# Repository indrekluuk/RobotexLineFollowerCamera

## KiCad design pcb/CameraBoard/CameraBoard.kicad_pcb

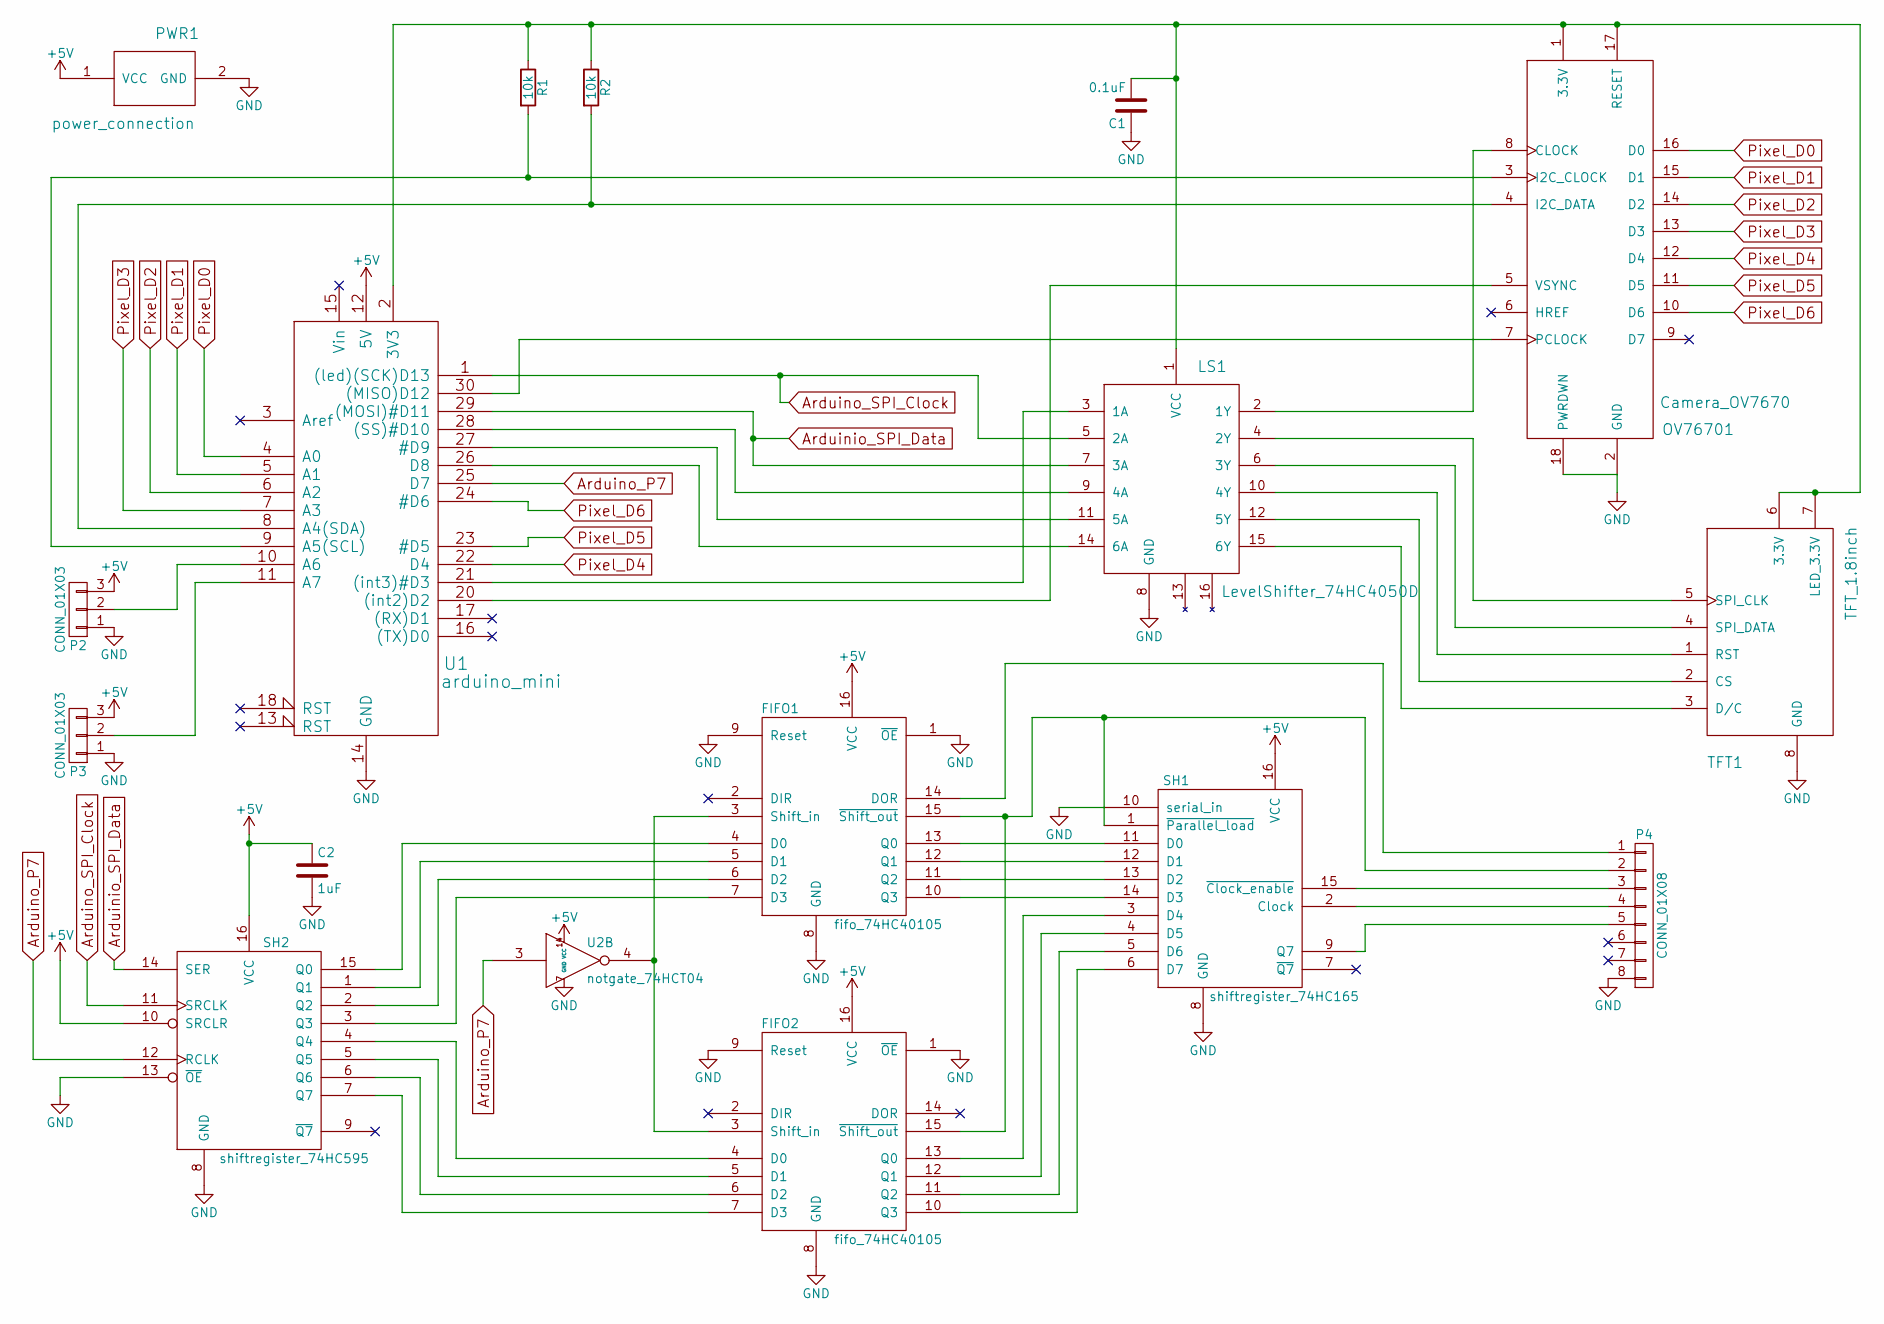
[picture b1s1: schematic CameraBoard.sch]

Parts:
C1: 0.1uF; C_1206_HandSoldering
C2: 1uF; C_1206_HandSoldering
FIFO1, FIFO2: fifo_74HC40105; SOIC-16_3.9x9.9mm_Pitch1.27mm
LS1: LevelShifter_74HC4050D; SOIC-16_3.9x9.9mm_Pitch1.27mm
OV76701: Camera_OV7670; Pin_Header_Straight_2x09
P2, P3: CONN_01X03; Pin_Header_Straight_1x03
P4: CONN_01X08; Pin_Header_Straight_2x04
PWR1: power_connection; Pin_Header_Straight_1x02
R1, R2: 10k; R_1206_HandSoldering
SH1: shiftregister_74HC165; SOIC-16_3.9x9.9mm_Pitch1.27mm
SH2: shiftregister_74HC595; SOIC-16_3.9x9.9mm_Pitch1.27mm
TFT1: TFT_1.8inch; Pin_Header_Straight_2x04
U1: arduino_mini
U2: notgate_74HCT04; SOIC-14_3.9x8.7mm_Pitch1.27mm

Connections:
+5V: C2.1, FIFO1.16 (VCC), FIFO2.16 (VCC), P2.3, P3.3, PWR1.1 (VCC), SH1.16 (VCC), SH2.10 (SRCLR), SH2.16 (VCC), U1.12 (5V), U2.14 (VCC)
Arduinio_SPI_Data: LS1.7 (3A), SH2.14 (SER), U1.29 ((MOSI)#D11)
Arduino_P7: SH2.12 (RCLK), U1.25 (D7), U2.3
Arduino_SPI_Clock: LS1.5 (2A), SH2.11 (SRCLK), U1.1 ((led)(SCK)D13)
GND: C1.1, C2.2, FIFO1.1 (~OE), FIFO1.8 (GND), FIFO1.9 (Reset), FIFO2.1 (~OE), FIFO2.8 (GND), FIFO2.9 (Reset), LS1.8 (GND), OV76701.2 (GND), OV76701.18 (PWRDWN), P2.1, P3.1, P4.8, PWR1.2 (GND), SH1.8 (GND), SH1.10 (serial_in), SH2.8 (GND), SH2.13 (~OE), TFT1.8 (GND), U1.14 (GND), U1.19 (GND), U2.7 (GND)
unnamed: C1.2, LS1.1 (VCC), OV76701.1 (3.3V), OV76701.17 (RESET), R1.1, R2.1, TFT1.6 (3.3V), TFT1.7 (LED_3.3V), U1.2 (3V3)
unnamed: FIFO1.3 (Shift_in), FIFO2.3 (Shift_in), U2.4
unnamed: FIFO1.4 (D0), SH2.15 (Q0)
unnamed: FIFO1.5 (D1), SH2.1 (Q1)
unnamed: FIFO1.6 (D2), SH2.2 (Q2)
unnamed: FIFO1.7 (D3), SH2.3 (Q3)
unnamed: FIFO1.10 (Q3), SH1.14 (D3)
unnamed: FIFO1.11 (Q2), SH1.13 (D2)
unnamed: FIFO1.12 (Q1), SH1.12 (D1)
unnamed: FIFO1.13 (Q0), SH1.11 (D0)
unnamed: FIFO1.14 (DOR), P4.1
unnamed: FIFO1.15 (~Shift_out), FIFO2.15 (~Shift_out), P4.2, SH1.1 (~Parallel_load)
unnamed: FIFO2.4 (D0), SH2.4 (Q4)
unnamed: FIFO2.5 (D1), SH2.5 (Q5)
unnamed: FIFO2.6 (D2), SH2.6 (Q6)
unnamed: FIFO2.7 (D3), SH2.7 (Q7)
unnamed: FIFO2.10 (Q3), SH1.6 (D7)
unnamed: FIFO2.11 (Q2), SH1.5 (D6)
unnamed: FIFO2.12 (Q1), SH1.4 (D5)
unnamed: FIFO2.13 (Q0), SH1.3 (D4)
unnamed: LS1.2 (1Y), OV76701.8 (CLOCK)
unnamed: LS1.3 (1A), U1.21 ((int3)#D3)
unnamed: LS1.4 (2Y), TFT1.5 (SPI_CLK)
unnamed: LS1.6 (3Y), TFT1.4 (SPI_DATA)
unnamed: LS1.9 (4A), U1.28 ((SS)#D10)
unnamed: LS1.10 (4Y), TFT1.1 (RST)
unnamed: LS1.11 (5A), U1.27 (#D9)
unnamed: LS1.12 (5Y), TFT1.2 (CS)
unnamed: LS1.14 (6A), U1.26 (D8)
unnamed: LS1.15 (6Y), TFT1.3 (D/C)
unnamed: OV76701.3 (I2C_CLOCK), R1.2, U1.9 (A5(SCL))
unnamed: OV76701.4 (I2C_DATA), R2.2, U1.8 (A4(SDA))
unnamed: OV76701.5 (VSYNC), U1.20 ((int2)D2)
unnamed: OV76701.7 (PCLOCK), U1.30 ((MISO)D12)
unnamed: P2.2, U1.10 (A6)
unnamed: P3.2, U1.11 (A7)
unnamed: P4.3, SH1.15 (~Clock_enable)
unnamed: P4.4, SH1.2 (Clock)
unnamed: P4.5, SH1.9 (Q7)
Pixel_D0: OV76701.16 (D0), U1.4 (A0)
Pixel_D1: OV76701.15 (D1), U1.5 (A1)
Pixel_D2: OV76701.14 (D2), U1.6 (A2)
Pixel_D3: OV76701.13 (D3), U1.7 (A3)
Pixel_D4: OV76701.12 (D4), U1.22 (D4)
Pixel_D5: OV76701.11 (D5), U1.23 (#D5)
Pixel_D6: OV76701.10 (D6), U1.24 (#D6)

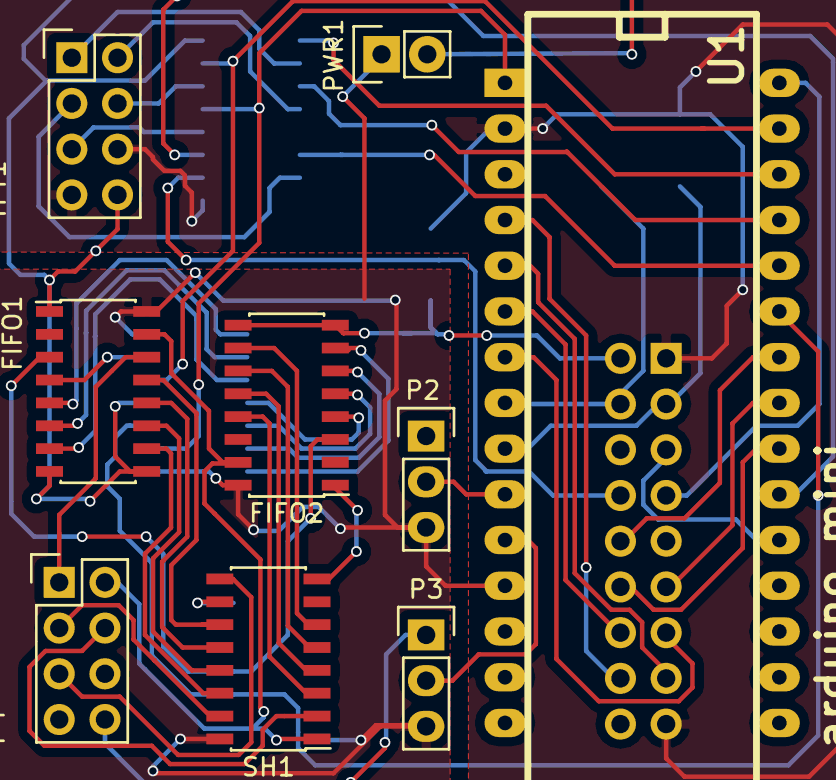
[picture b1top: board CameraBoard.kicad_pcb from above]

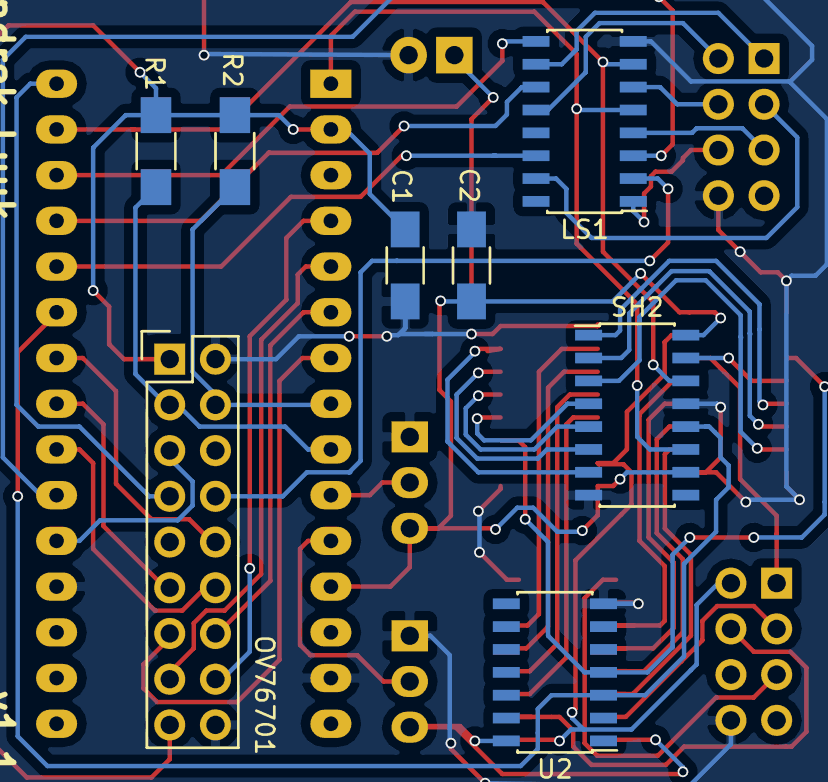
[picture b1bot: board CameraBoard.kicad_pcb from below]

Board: 2 copper layers, 17 parts (8 on the bottom side), 51 nets.

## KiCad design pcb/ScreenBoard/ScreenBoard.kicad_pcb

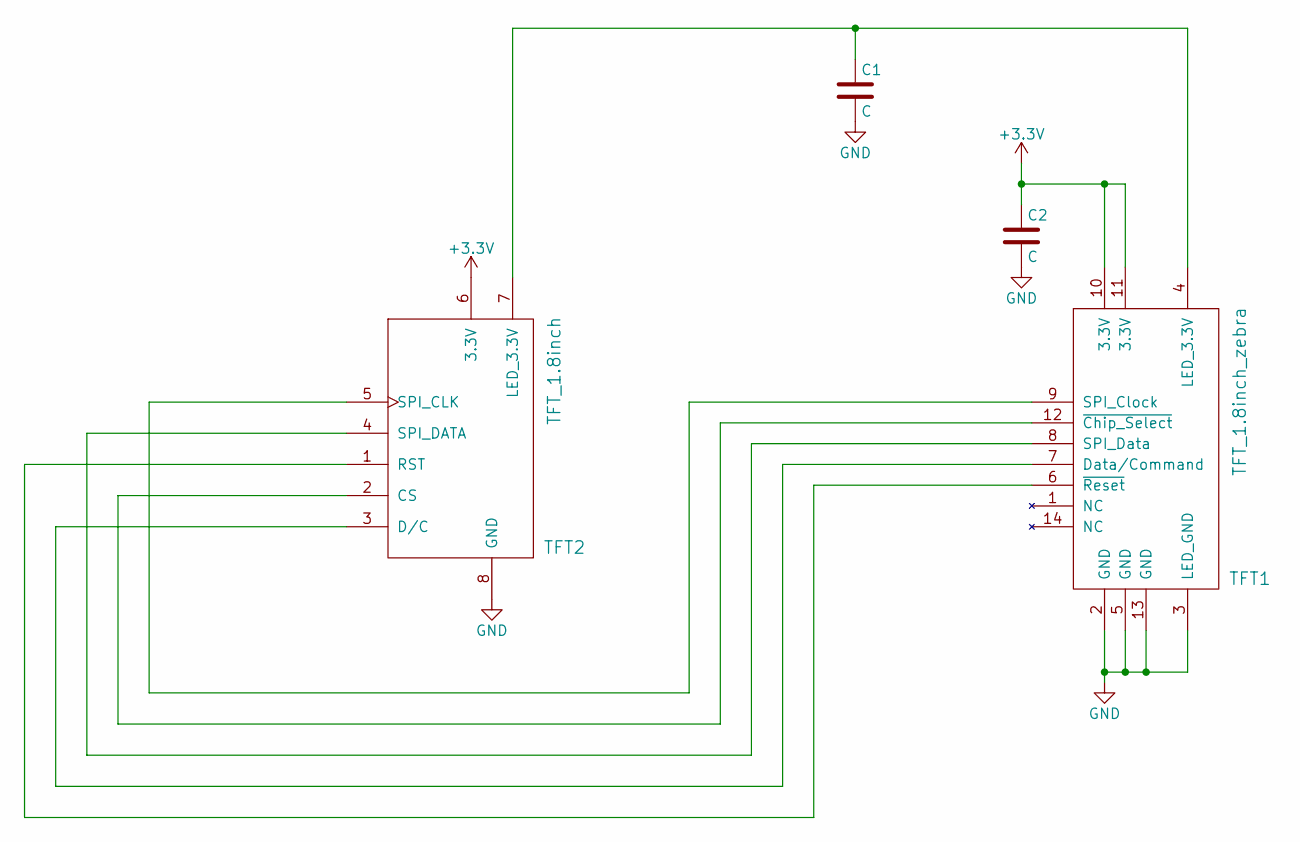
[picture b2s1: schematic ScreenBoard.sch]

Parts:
C1, C2: C; C_1206_HandSoldering
TFT1: TFT_1.8inch_zebra; ZebraStrip14_0.8mm
TFT2: TFT_1.8inch; Pin_Header_Straight_2x04

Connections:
+3V3: C2.1, TFT1.10 (3.3V), TFT1.11 (3.3V), TFT2.6 (3.3V)
GND: C1.2, C2.2, TFT1.2 (GND), TFT1.3 (LED_GND), TFT1.5 (GND), TFT1.13 (GND), TFT2.8 (GND)
unnamed: C1.1, TFT1.4 (LED_3.3V), TFT2.7 (LED_3.3V)
unnamed: TFT1.6 (~Reset), TFT2.1 (RST)
unnamed: TFT1.7 (Data/Command), TFT2.3 (D/C)
unnamed: TFT1.8 (SPI_Data), TFT2.4 (SPI_DATA)
unnamed: TFT1.9 (SPI_Clock), TFT2.5 (SPI_CLK)
unnamed: TFT1.12 (~Chip_Select), TFT2.2 (CS)

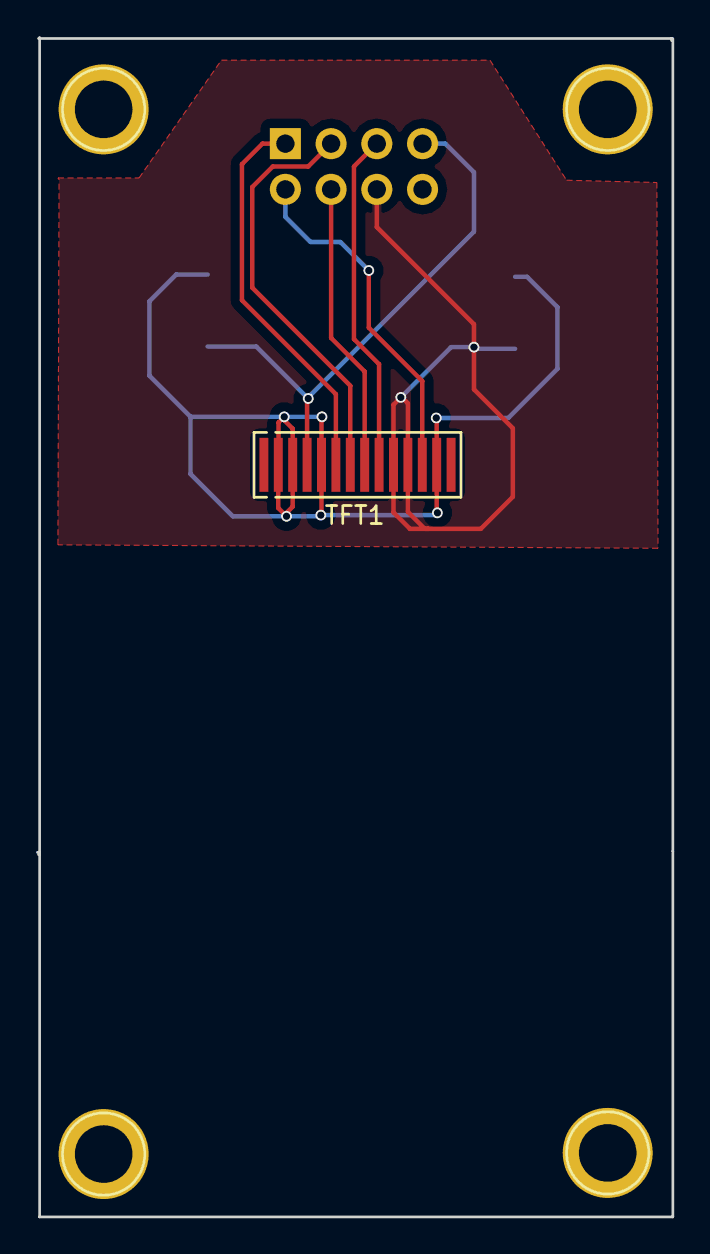
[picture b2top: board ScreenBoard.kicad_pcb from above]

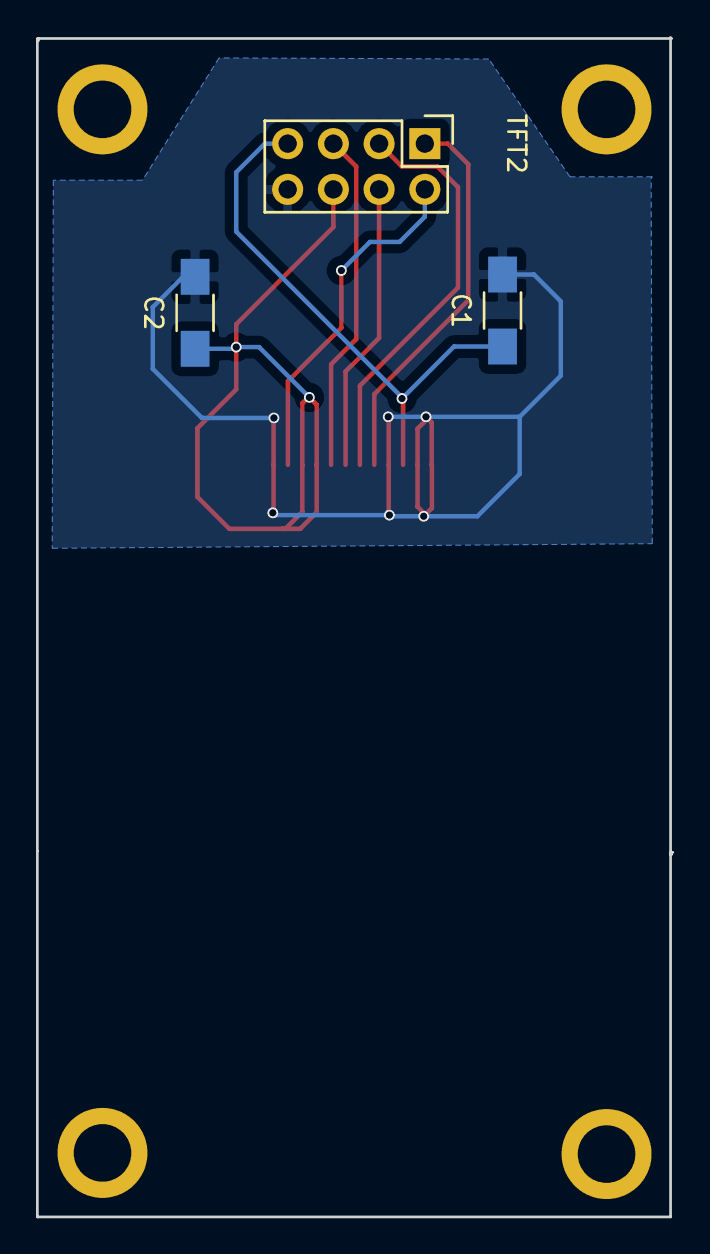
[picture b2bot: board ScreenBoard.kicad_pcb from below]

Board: 2 copper layers, 35.3 x 65.5 mm, 4 parts (3 on the bottom side), 8 nets.

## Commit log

2016-04-26 working grayscale
2016-04-26 optimized greyscale
2016-04-26 added RGB greyscale table
2016-04-30 renamed files
2016-04-30 resultion specific class
2016-04-30 camera code separated to its own file
2016-04-30 virtual function to force compile time method check
2016-04-30 configure pixel format
2016-04-30 move code to header file
2016-04-30 moved buffering to template
2016-04-30 Pixel buffer with shifted output
2016-04-30 removed unnecessary file
2016-04-30 separated grayscale table to its own file
2016-04-30 5Hz with loop
2016-04-30 unified class for below 10hz
2016-04-30 wait for 5Hz
2016-04-30 code clean-up
2016-05-07 updated camera library
2016-05-07 calculate average
2016-05-07 refactored main file
2016-05-08 improvements
2016-05-08 optimized
2016-05-08 reduce monochrome resolution to get more calculation time
2016-05-11 method for reversing bits
2016-05-13 added PCB - in progress
2016-05-15 PCB with FIFO
2016-05-15 PCB footprints are not set
2016-05-15 PCB fully wired
2016-05-16 generated gerber files
2016-06-11 Fixed NOT gate footprint
2016-07-10 moved camera board pcb to sub-folder
2016-07-10 added screen board
2016-07-10 removed labels from screw holes
2016-09-07 code is now working with new camera board
2016-09-20 send data to shift register
2016-10-02 renamed methods
2016-10-03 fixed PCB
2016-10-30 init all camera related items at one place
2016-10-30 restructured project
2016-10-30 added gtest to project
2016-10-30 added working example tests
2016-11-06 refactored code
2016-11-06 template buffer size type
2016-11-06 removed unnecessary parameters
2016-11-06 smaller buffer for grayscale
2016-11-06 camera library update
2016-11-06 ignore pdf
2016-11-06 buffer shift is not necessary from black and white image
2016-11-06 methods for writing grayscale bytes to screen
2016-11-06 alternating monochrome and grayscale lines
2016-11-06 line index
2016-11-07 new buffered camera for 80x120 grayscale
2016-11-07 separate buffer for monochrome
2016-11-08 send line location over data bus
2016-11-08 working solution
2016-11-12 14 bit monochrome buffer
2016-11-12 send pixel line over data line
2016-11-12 shifted lower byte by one
2016-11-13 removed line
2016-11-13 optimized screen cycles
2016-11-13 faster addressStart
2016-11-13 removed duplicated code
2016-11-13 reorganized code
2016-11-14 preparations for line detection
2016-11-15 re-organized CMakeLists.txt
2016-11-15 test line
2016-11-16 line detection working
2016-11-16 line as template
2016-11-16 follow connected line
2016-11-19 fixed pixel delay
2016-11-20 step detection
2016-11-20 process by segments
2016-11-20 wider line
2016-11-20 line
2016-11-20 fixed rowIndex
2016-11-20 fixed row detection if no row from the start of the screen
2016-11-20 fixed split
2016-11-20 fixed line if segments didn't touch
2016-11-20 removed duplicating test
2016-11-20 fixed start looking for line at the mid-point
2016-11-20 refactored LineStep to its own file
2016-11-20 step continuation
2016-11-20 better connection check
2016-11-20 get minimum to edge
2016-11-20 fixed typo
2016-11-20 alternating pixel color
2016-11-22 unified names
2016-11-22 ignore generated files
2016-11-23 new slope calculation
2016-11-23 fixed blue line
2016-11-23 first screen test
2016-11-24 captured screen test
2016-11-24 first screen capture test successful
2016-11-24 fixed slope calculation
2016-11-24 spreadsheet for slope calculation
2016-11-24 send line for capture
2016-11-24 fixed data mask
2016-11-25 print calculated slope value
2016-11-25 fixed bottom slope calculation
2016-11-25 adjusted slope delta
2016-11-25 but back inline attribute
2016-11-25 test case 3
2016-11-25 test case 4
2016-11-25 test case 5 (failing)
2016-11-26 new edge detection logic
2016-11-26 moved screen test to separate class
2016-11-26 all tests passing
2016-11-26 additional tests
2016-11-26 fixed line edge reset
2016-11-26 if first step is longer than the second step then use that as a reference
2016-11-26 fixed first step position value
2016-11-26 first step can not start from the edge of the screen
2016-11-26 ignore first line
2016-11-26 ignore first 5 lines
2016-11-26 send identified line
2016-11-26 frame capture printout directly in camera Arduino
2016-11-27 removed unnecessary comments
2016-11-27 do not start line if it is detected from bottom corners (camera can see the wheel)
2016-11-28 lower threshold for line detection
2016-11-28 16 line stripes
2016-11-28 if line is already found then do disable corner disabling
2016-11-28 move detected line to edge if line segment touches edge
2016-11-29 minimum line detection start range
2016-11-29 fixed tests
2016-11-29 use bitfield structure for message
2016-11-29 store before and after segments
2016-11-29 removed red lines
2016-11-29 detect sharp turn
2016-11-29 fixed sharp turn direction
2016-11-29 detect segment jump
2016-11-30 removed sharp turn detection. Too flaky
2016-11-30 detect crossing
2016-11-30 remove turn detection delay
2016-11-30 failing test for line split
2016-11-30 renamed class
2016-11-30 refactored inner structure
2016-11-30 split sections
2016-11-30 detect split
2016-12-01 process line split
2016-12-01 fixed end of line
2016-12-01 improved split line printout
2016-12-01 stop Line after line found
2016-12-01 split detection fix
2016-12-01 80 pixel grayscale does not need unrolled pixel reading
2016-12-01 fixed split detection
2016-12-01 renamed methods to be more descriptive
2016-12-01 fixed all tests
2016-12-01 fixed grayscale image
2016-12-01 restore ignore zone
2016-12-02 moved line turn ignore check to more correct location
2016-12-02 cancel line search if line jump
2016-12-02 fixed line detection if line takes whole screen
2016-12-02 for second line choose closest to middle
2016-12-02 make row top more visible
2016-12-02 use segment center after split detection
2016-12-02 for sub-sequent splits choose closest to the middle
2016-12-02 do not force line to edge
2016-12-02 show identified line
2016-12-02 turn on capture mode
2016-12-02 send dummy line if no line found
2018-07-14 Image of the robot
